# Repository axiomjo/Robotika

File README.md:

# Robotika
UAS Pemrograman Robotika.

Soal praktik UAS Pemrograman Robotika.

RC Car dengan ukuran kecil.

Specs:
1. MCU = WeMos D1 Mini (ESP8266)
2. Drive motors = DC Motor
3. Motor driver = L293D
4. RGB lights = WS2812B Smart LED Strip RGB

To-Do:
1. steering = pakai program / pwm
2. led strip, added to pcb, program?

Update:
14/4/2024 - PCB done, 2 versions available: With/without LED using 4 wire SPI

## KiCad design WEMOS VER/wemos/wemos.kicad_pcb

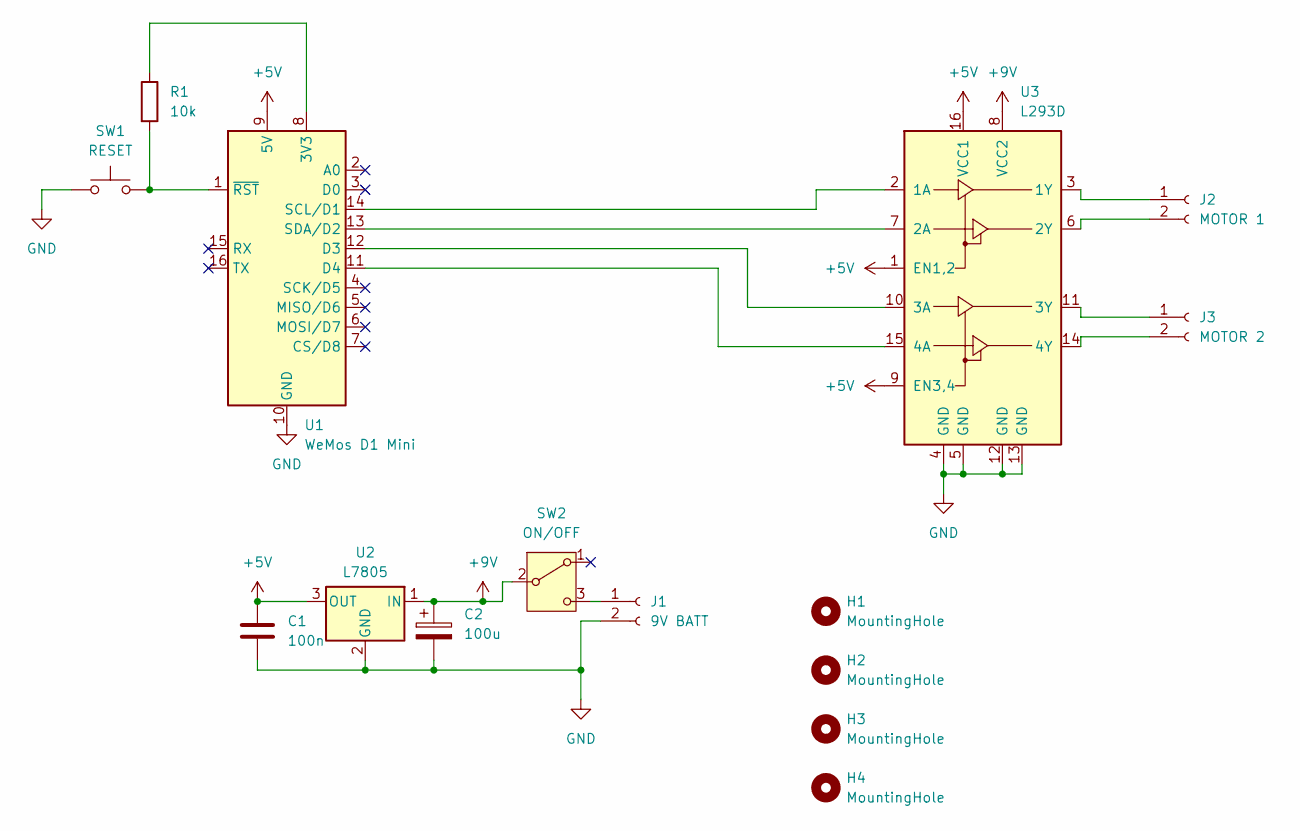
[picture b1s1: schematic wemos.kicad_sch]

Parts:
C1: 100n; C_Disc_D5.0mm_W2.5mm_P5.00mm
C2: 100u; CP_Radial_D5.0mm_P2.50mm
H1, H2, H3, H4: MountingHole; MountingHole_3.2mm_M3
J1: 9V BATT; PinHeader_1x02_P2.54mm_Vertical
J2: MOTOR 1; PinHeader_1x02_P2.54mm_Vertical
J3: MOTOR 2; PinHeader_1x02_P2.54mm_Vertical
R1: 10k; R_Axial_DIN0207_L6.3mm_D2.5mm_P7.62mm_Horizontal
SW1: RESET; SW_PUSH_6mm
SW2: ON/OFF; PinSocket_1x03_P2.54mm_Vertical
U1: WeMos D1 Mini; WEMOS_D1_mini_light
U2: L7805; TO-220-3_Vertical
U3: L293D; DIP-16_W7.62mm

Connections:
+5V: C1.1, U1.9 (5V), U2.3 (OUT), U3.1 (EN1,2), U3.9 (EN3,4), U3.16 (VCC1)
+9V: C2.1, SW2.2 (B), U2.1 (IN), U3.8 (VCC2)
GND: C1.2, C2.2, J1.2, SW1.1, U1.10 (GND), U2.2 (GND), U3.4 (GND), U3.5 (GND), U3.12 (GND), U3.13 (GND)
unnamed: J1.1, SW2.3 (C)
unnamed: J2.1, U3.3 (1Y)
unnamed: J2.2, U3.6 (2Y)
unnamed: J3.1, U3.11 (3Y)
unnamed: J3.2, U3.14 (4Y)
unnamed: R1.1, U1.8 (3V3)
unnamed: U1.12 (D3), U3.10 (3A)
unnamed: U1.11 (D4), U3.15 (4A)
unnamed: U1.14 (SCL/D1), U3.2 (1A)
unnamed: U1.13 (SDA/D2), U3.7 (2A)
unnamed: R1.2, SW1.2, U1.1 (~RST)

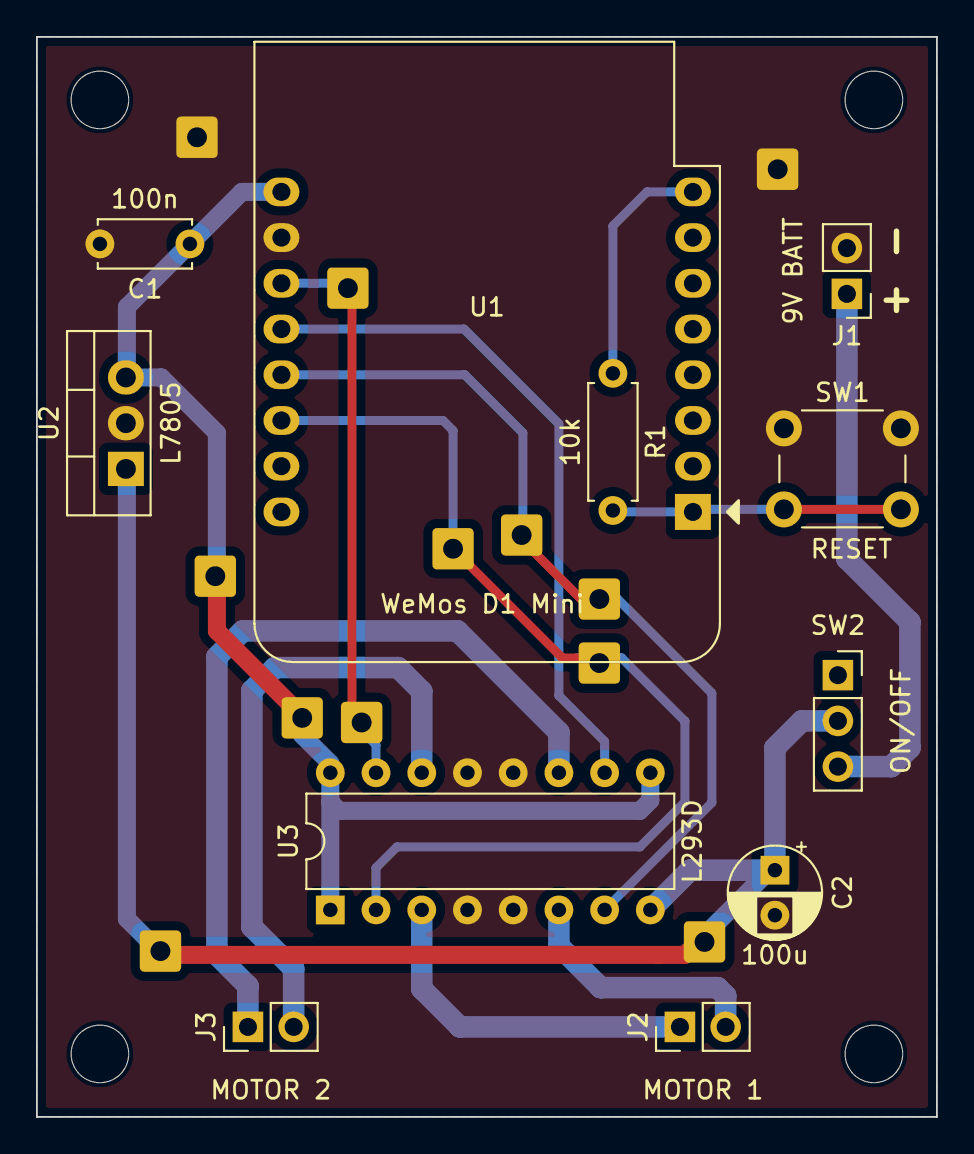
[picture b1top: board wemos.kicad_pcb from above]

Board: 2 copper layers, 50.0 x 60.0 mm, 15 parts (0 on the bottom side), 14 nets.

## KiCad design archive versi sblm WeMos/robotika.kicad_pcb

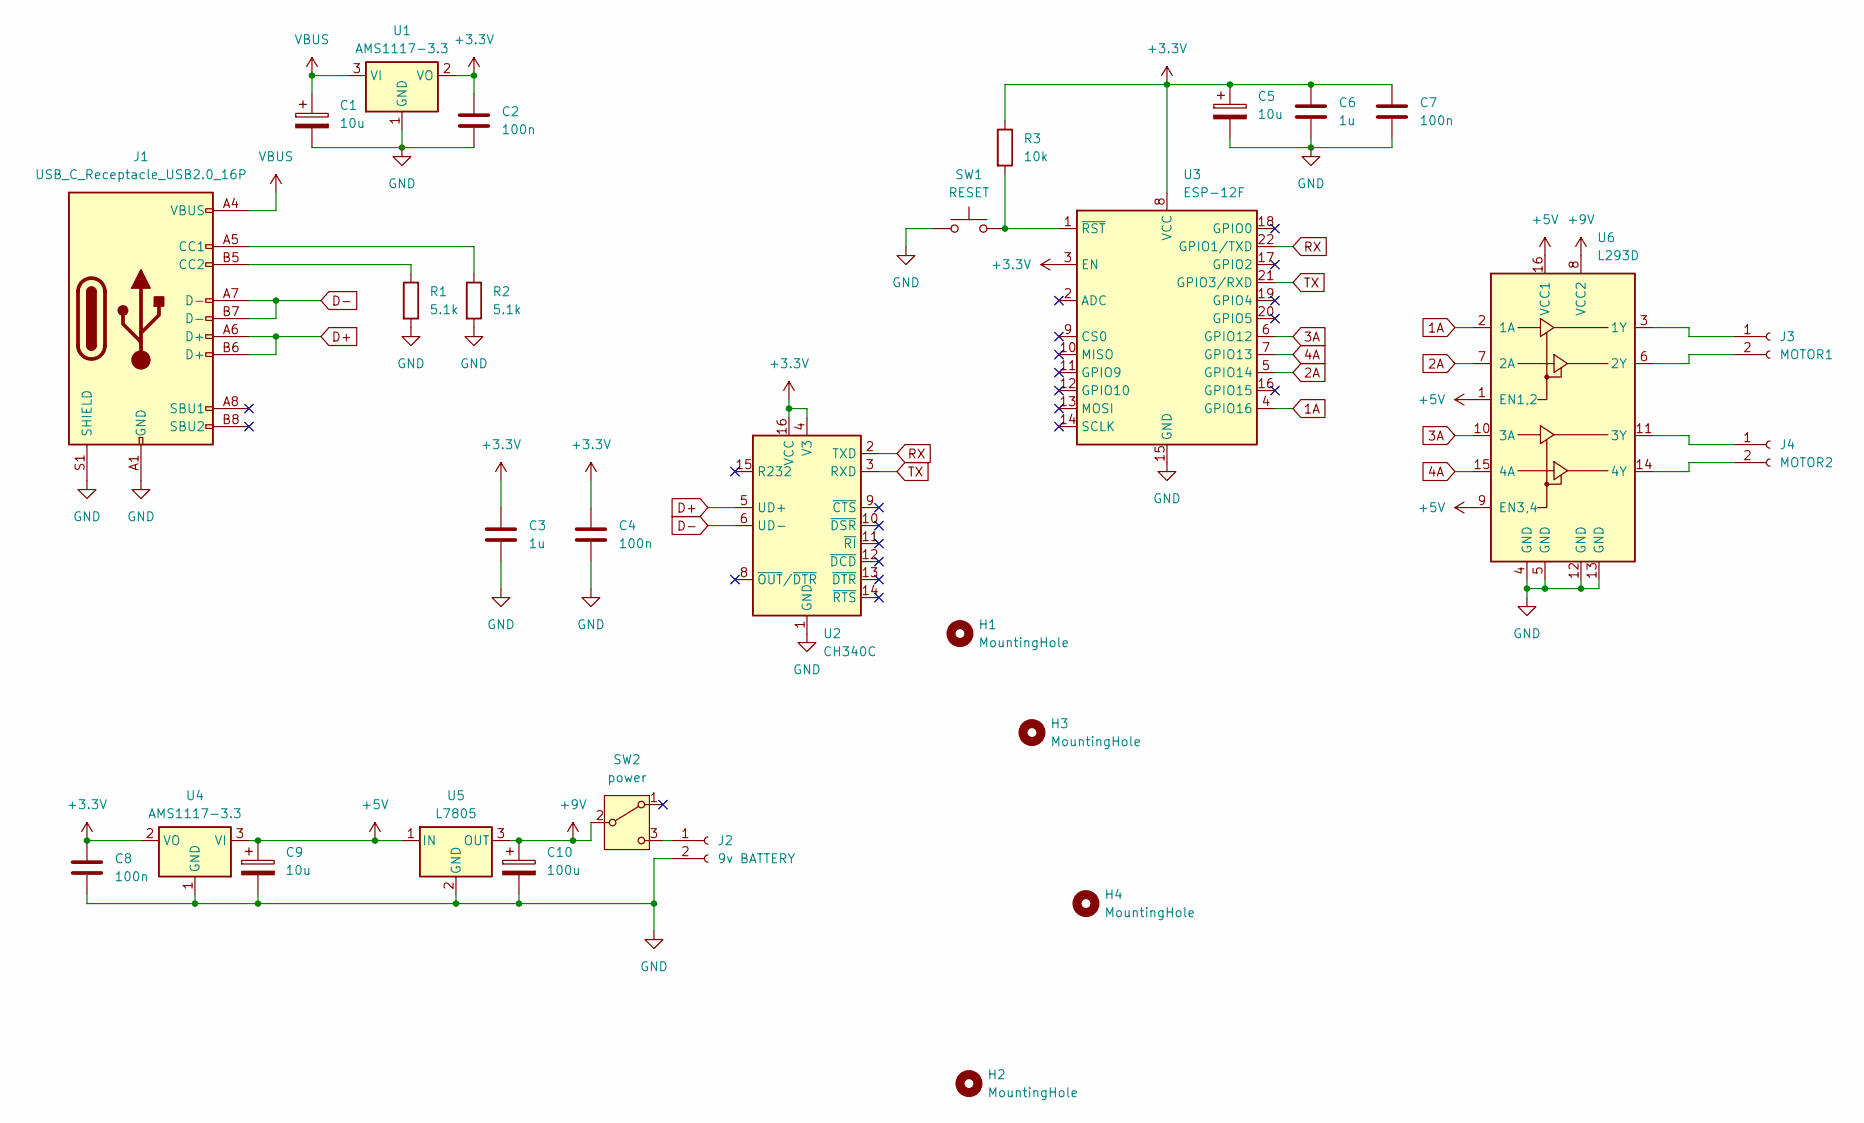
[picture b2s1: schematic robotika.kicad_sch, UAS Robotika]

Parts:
C1, C5, C9: 10u; CP_Radial_D5.0mm_P2.50mm
C2, C4, C7, C8: 100n; C_0805_2012Metric_Pad1.18x1.45mm_HandSolder
C3, C6: 1u; C_0805_2012Metric_Pad1.18x1.45mm_HandSolder
C10: 100u; CP_Radial_D5.0mm_P2.50mm
H1, H2, H3, H4: MountingHole; MountingHole_3.2mm_M3
J1: USB_C_Receptacle_USB2.0_16P; USB_C_Receptacle_XKB_U262-16XN-4BVC11
J2: 9v BATTERY; PinHeader_1x02_P2.54mm_Vertical
J3: MOTOR1; PinHeader_1x02_P2.54mm_Vertical
J4: MOTOR2; PinHeader_1x02_P2.54mm_Vertical
R1, R2: 5.1k; R_0805_2012Metric_Pad1.20x1.40mm_HandSolder
R3: 10k; R_0805_2012Metric_Pad1.20x1.40mm_HandSolder
SW1: RESET; SW_PUSH_6mm
SW2: power; PinSocket_1x03_P2.54mm_Vertical
U1, U4: AMS1117-3.3; SOT-223-3_TabPin2
U2: CH340C; SOIC-16_3.9x9.9mm_P1.27mm
U3: ESP-12F; ESP-12E
U5: L7805; TO-263-2
U6: L293D; DIP-16_W7.62mm

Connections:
1A: U3.4 (GPIO16), U6.2 (1A)
2A: U3.5 (GPIO14), U6.7 (2A)
3A: U3.6 (GPIO12), U6.10 (3A)
4A: U3.7 (GPIO13), U6.15 (4A)
+3.3V: C2.1, C3.1, C4.1, C5.1, C6.1, C7.1, C8.1, R3.1, U1.2 (VO), U2.4 (V3), U2.16 (VCC), U3.3 (EN), U3.8 (VCC), U4.2 (VO)
+5V: C9.1, U4.3 (VI), U5.1 (IN), U6.1 (EN1,2), U6.9 (EN3,4), U6.16 (VCC1)
+9V: C10.1, SW2.2 (B), U5.3 (OUT), U6.8 (VCC2)
D+: J1.A6 (D+), J1.B6 (D+), U2.5 (UD+)
D-: J1.A7 (D-), J1.B7 (D-), U2.6 (UD-)
GND: C1.2, C2.2, C3.2, C4.2, C5.2, C6.2, C7.2, C8.2, C9.2, C10.2, J1.A1 (GND), J1.A12 (GND), J1.B1 (GND), J1.B12 (GND), J1.S1 (SHIELD), J2.2, R1.2, R2.2, SW1.1, U1.1 (GND), U2.1 (GND), U3.15 (GND), U4.1 (GND), U5.2 (GND), U6.4 (GND), U6.5 (GND), U6.12 (GND), U6.13 (GND)
unnamed: J1.A5 (CC1), R2.1
unnamed: J1.B5 (CC2), R1.1
unnamed: J2.1, SW2.3 (C)
unnamed: J3.1, U6.3 (1Y)
unnamed: J3.2, U6.6 (2Y)
unnamed: J4.1, U6.11 (3Y)
unnamed: J4.2, U6.14 (4Y)
unnamed: R3.2, SW1.2, U3.1 (~RST)
RX: U2.2 (TXD), U3.22 (GPIO1/TXD)
TX: U2.3 (RXD), U3.21 (GPIO3/RXD)
VBUS: C1.1, J1.A4 (VBUS), J1.A9 (VBUS), J1.B4 (VBUS), J1.B9 (VBUS), U1.3 (VI)

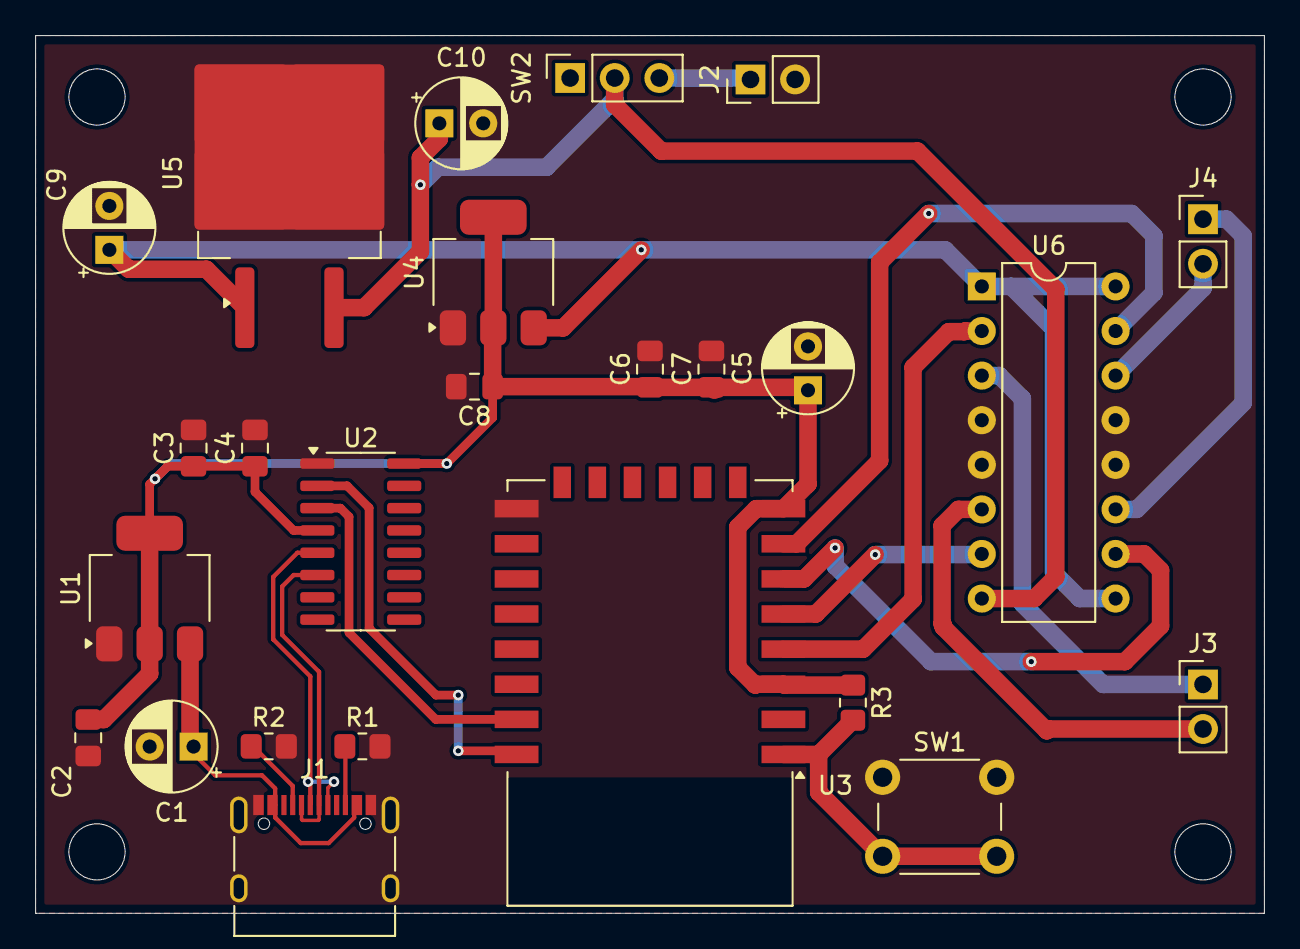
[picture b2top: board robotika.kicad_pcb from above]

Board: 2 copper layers, 70.0 x 50.0 mm, 29 parts (0 on the bottom side), 21 nets.

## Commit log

2024-04-05 MD Update
2024-04-05 Update MD 2
2024-04-05 Schematic Upload
    Revision 1 of the schematic, no layout, changes to MD
2024-04-05 MD Changes
2024-04-05 MD Change
2024-04-05 Schematic A4 Upload
    Uploaded a A4 printable version of the schematic
2024-04-05 MD Update And File Name Changes
    Updated MD and changed the file name for the schematic
2024-04-05 Schematic Update 2
2024-04-11 A LOT OF WORK DONE
    Added a version using WeMos D1 Mini
2024-04-12 Add files via upload
    tambahin ss pcb dari file Kicad clief & sketsa bentuk RC car nya.
    version Jumat 12 April 2024
2024-04-12 Create inicumaplaceholdersupayabisabikinfolderwkwkwk
    sblm WeMos
2024-04-12 pindah tempat tok
2024-04-12 pindah tempat tok (ptt)
2024-04-12 Create gtwya
2024-04-12 nambahin oret2an jojo
2024-04-13 more oret-oretan jojo
2024-04-13 gambar oret2an jojo
2024-04-13 nghapus placeholder toj
2024-04-13 nghapus placeholder tok
2024-04-13 OLD version history archive aja seh
2024-04-13 sketsa yg lebih baru Sabtu, 13 April
2024-04-14 A LOT OF WORK
2024-04-15 blom ngoding, masih di oret-oretan jojo
    perlu ke perpus sblm robotika rabu AAAAAAAAAAAAAA
2024-04-16 work
2024-04-17 rekues nggabung proyek robotika dengan proyek robotik AHAHAHAHA
2024-04-21 slight changes
2024-04-22 nemu repo FSM & software bikin UI drag n drop
    tengkyu dah nalangin beli modulnya dulu.
    terimakasih dah ngecarry pas aku AFK. maaf aku AFK kelamaan.
    berhubung rabu kunjungan pabrik,
    kamis ini jam 23:59 aku berencana ngupload prototype wemos nya + sketsa state machinenya
    karena prak baru kelar hari rabu sore ini🙏
2024-04-22 slight change to pcb
2024-04-22 pdf pcb
2024-04-23 oret2an udh g kepake, pake file baru
2024-04-23 folder brainstorming program
2024-04-23 salah floder
2024-04-23 penjelasan plan softwarenya gmn
2024-04-23 supaya bisa esp8266 di arduino ide
2024-04-23 supaya bisa wifi
2024-04-23 libraries & resources keren dari org2 lain yg dipake buat RC Car Mendako Bocchi
2024-04-23 buat .ino
2024-04-23 nambahin lembar kerja tok. blom diisi
    kutambahin pas mdp
2024-04-23 sepotong state machine yg mau di-implement
2024-04-27 web work
2024-04-27 esp and web
2024-04-27 current plan oret2an
